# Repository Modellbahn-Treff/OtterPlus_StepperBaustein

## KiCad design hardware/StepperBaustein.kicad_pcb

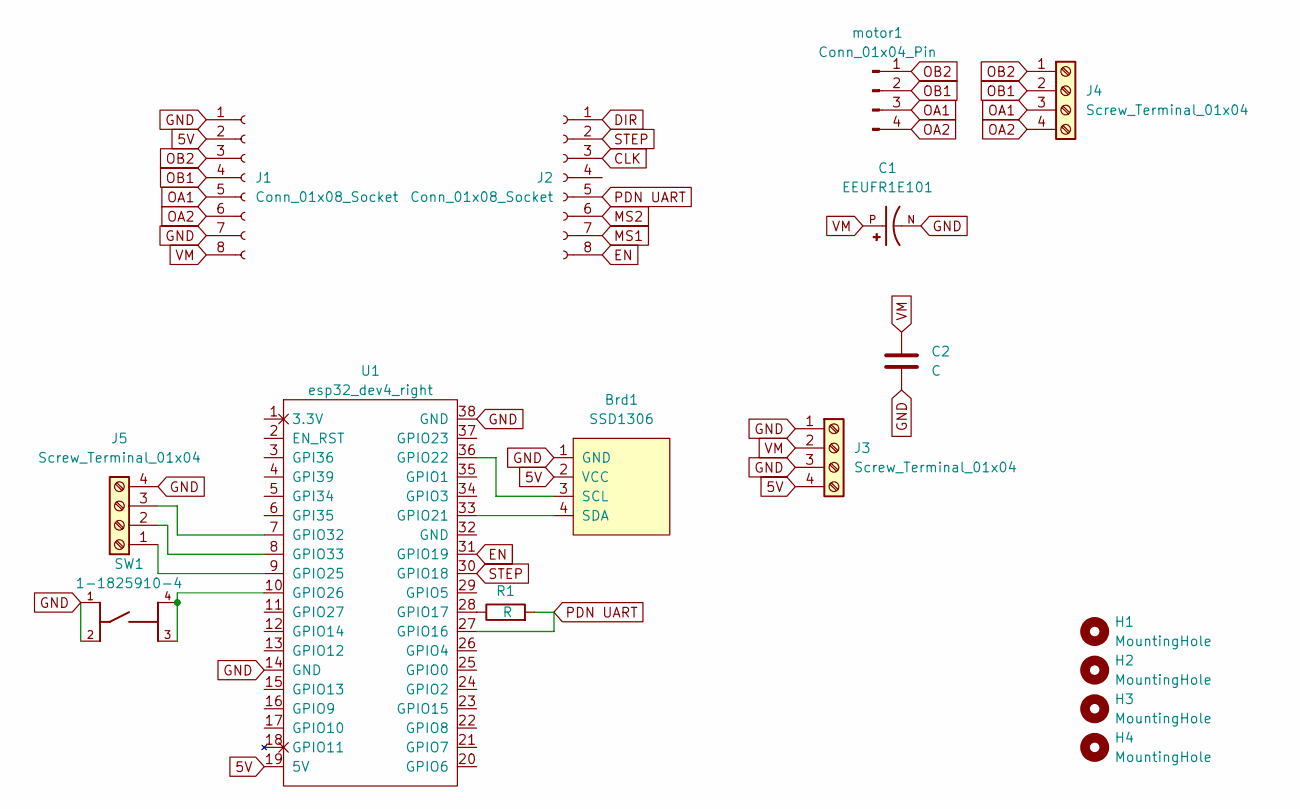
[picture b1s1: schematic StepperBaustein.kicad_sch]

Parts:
Brd1: SSD1306; 128x64OLED
C1: EEUFR1E101; CAPPRD250W50D630H1120; PARTREV 28-FEB-20
C2: C; C_0805_2012Metric_Pad1.18x1.45mm_HandSolder
H1, H2, H3, H4: MountingHole; MountingHole_3.2mm_M3
J1, J2: Conn_01x08_Socket; PinSocket_1x08_P2.54mm_Vertical
J3, J4, J5: Screw_Terminal_01x04; 1729144
R1: R; R_0805_2012Metric_Pad1.20x1.40mm_HandSolder
SW1: 1-1825910-4; TE_1-1825910-4; PARTREV C10
U1: esp32_dev4_right
U2: esp32_dev4_left; esp32_dev_left
motor1: Conn_01x04_Pin; PinSocket_1x04_P2.54mm_Vertical

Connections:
5V: Brd1.2 (VCC), J1.2, J3.4, U2.19 (5V)
CLK: J2.3
DIR: J2.1
EN: J2.8, U1.31 (GPIO19)
GND: Brd1.1 (GND), C1.N, C2.2, J1.1, J1.7, J3.1, J3.3, J5.4, SW1.1, SW1.2, U1.38 (GND), U2.14 (GND)
MS1: J2.7
MS2: J2.6
unnamed: Brd1.3 (SCL), U1.36 (GPIO22)
unnamed: Brd1.4 (SDA), U1.33 (GPIO21)
unnamed: J5.1, U2.9 (GPIO25)
unnamed: J5.2, U2.8 (GPIO33)
unnamed: J5.3, U2.7 (GPIO32)
unnamed: R1.1, U1.28 (GPIO17)
unnamed: SW1.3, SW1.4, U2.10 (GPIO26)
OA1: J1.5, J4.3, motor1.3
OA2: J1.6, J4.4, motor1.4
OB1: J1.4, J4.2, motor1.2
OB2: J1.3, J4.1, motor1.1
PDN UART: J2.5, R1.2, U1.27 (GPIO16)
STEP: J2.2, U1.30 (GPIO18)
VM: C1.P, C2.1, J1.8, J3.2

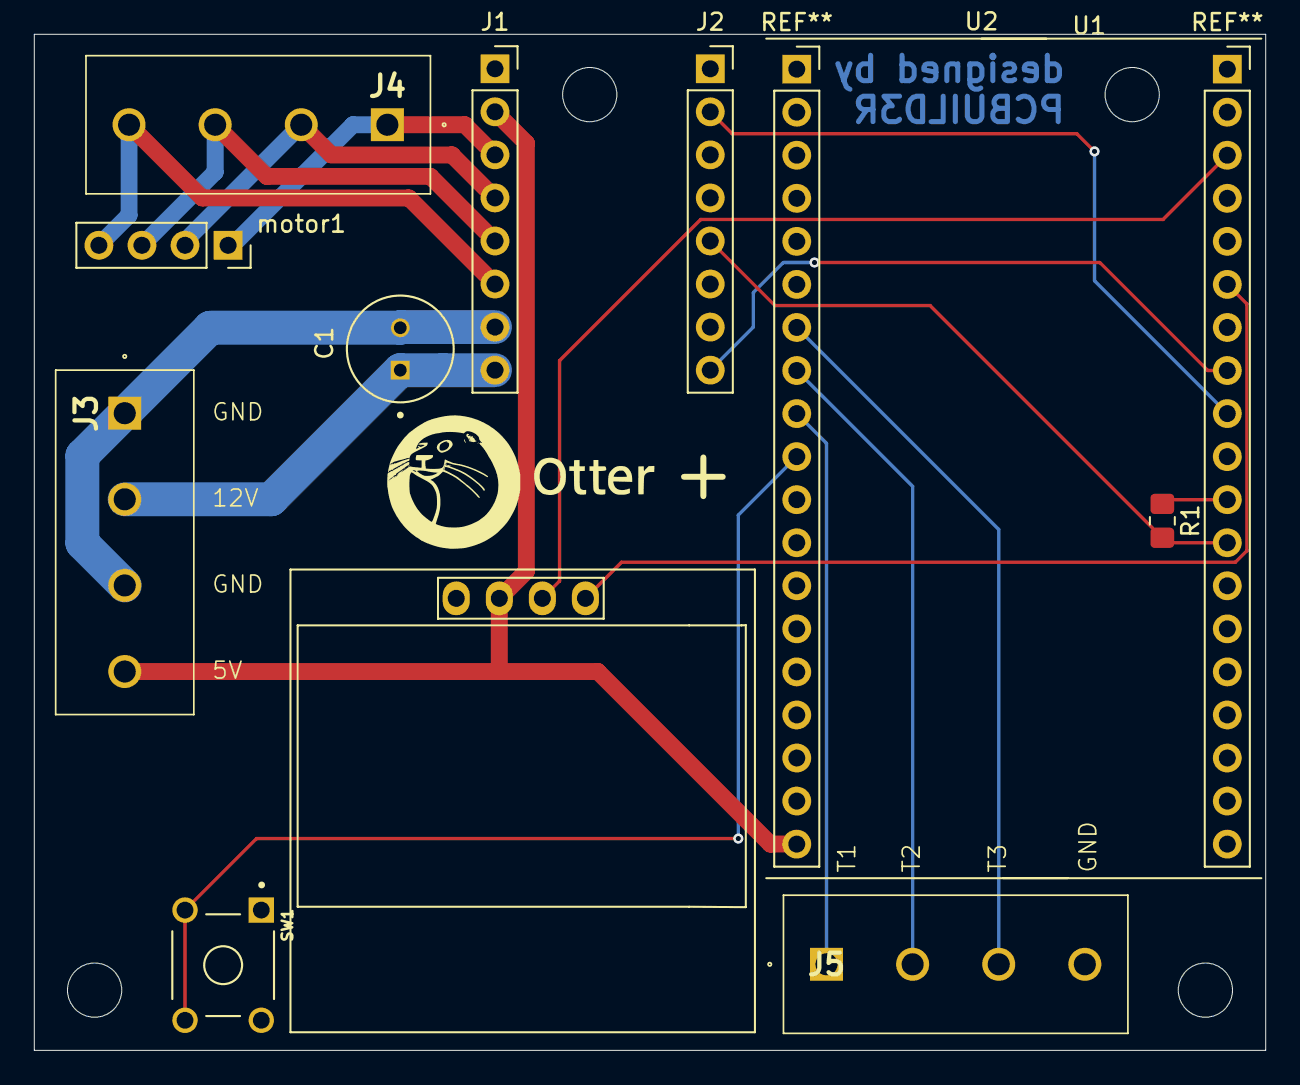
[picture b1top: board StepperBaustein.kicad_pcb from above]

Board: 2 copper layers, 72.6 x 59.9 mm, 17 parts (1 on the bottom side), 17 nets.

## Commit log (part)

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2026-05-02 Add .gitignore
2026-06-20 create firmware folder
2026-06-27 Add firmware
2026-06-27 Add initial build and deployment workflow, HTML interface, and manifest file
2026-06-27 Fix gpio input configuration type
2026-06-27 deploy: 0b154b66fbf33360761660c8182ad4eefb517397
2026-06-27 Update MQTT publish status function to enable QoS and retain message
2026-06-27 Implement screen navigation and update display function to include IP address
2026-06-27 deploy: 764ff19bbf270d77725645b23c4f99c7cf121227
